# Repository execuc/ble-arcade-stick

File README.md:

BLUETOOTH ARCADE STICK
==========

Project in three part to create a bluetooth arcade stick:
 * [PCB](https://github.com/execuc/ble-arcade-stick/tree/master/pcb)
 * [Bluetooth firmware on NRF51822](https://github.com/execuc/ble-arcade-stick/tree/master/firmware)
 * [Laser cut enclosure with FreeCAD](https://github.com/execuc/ble-arcade-stick/tree/master/cad)

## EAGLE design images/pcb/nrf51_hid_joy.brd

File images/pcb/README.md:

BLUETOOTH ARCADE OR JOYSTICK PCB CONTROLLER
==========

This part contains schematic, layout and gerber files to produce a bluetooth arcade or joystick controller. It is
based on Waveshare NRF51822 module. PCB is made with EAGLE software.

**Caution** : The PCB has not been tested yet.
**Caution** : No reverse polarity

Files
--------------------

 * nrf51_hid_joy.lbr : EAGLE library.
 * nrf51_hid_joy.sch : EAGLE schematic.
 * nrf51_hid_joy.brd : EAGLE board.
 * nrf51_hid_joy.zip : gerber files for PCB.

DIMENSION
--------------------

TODO
--------------------

 * Test PCB.

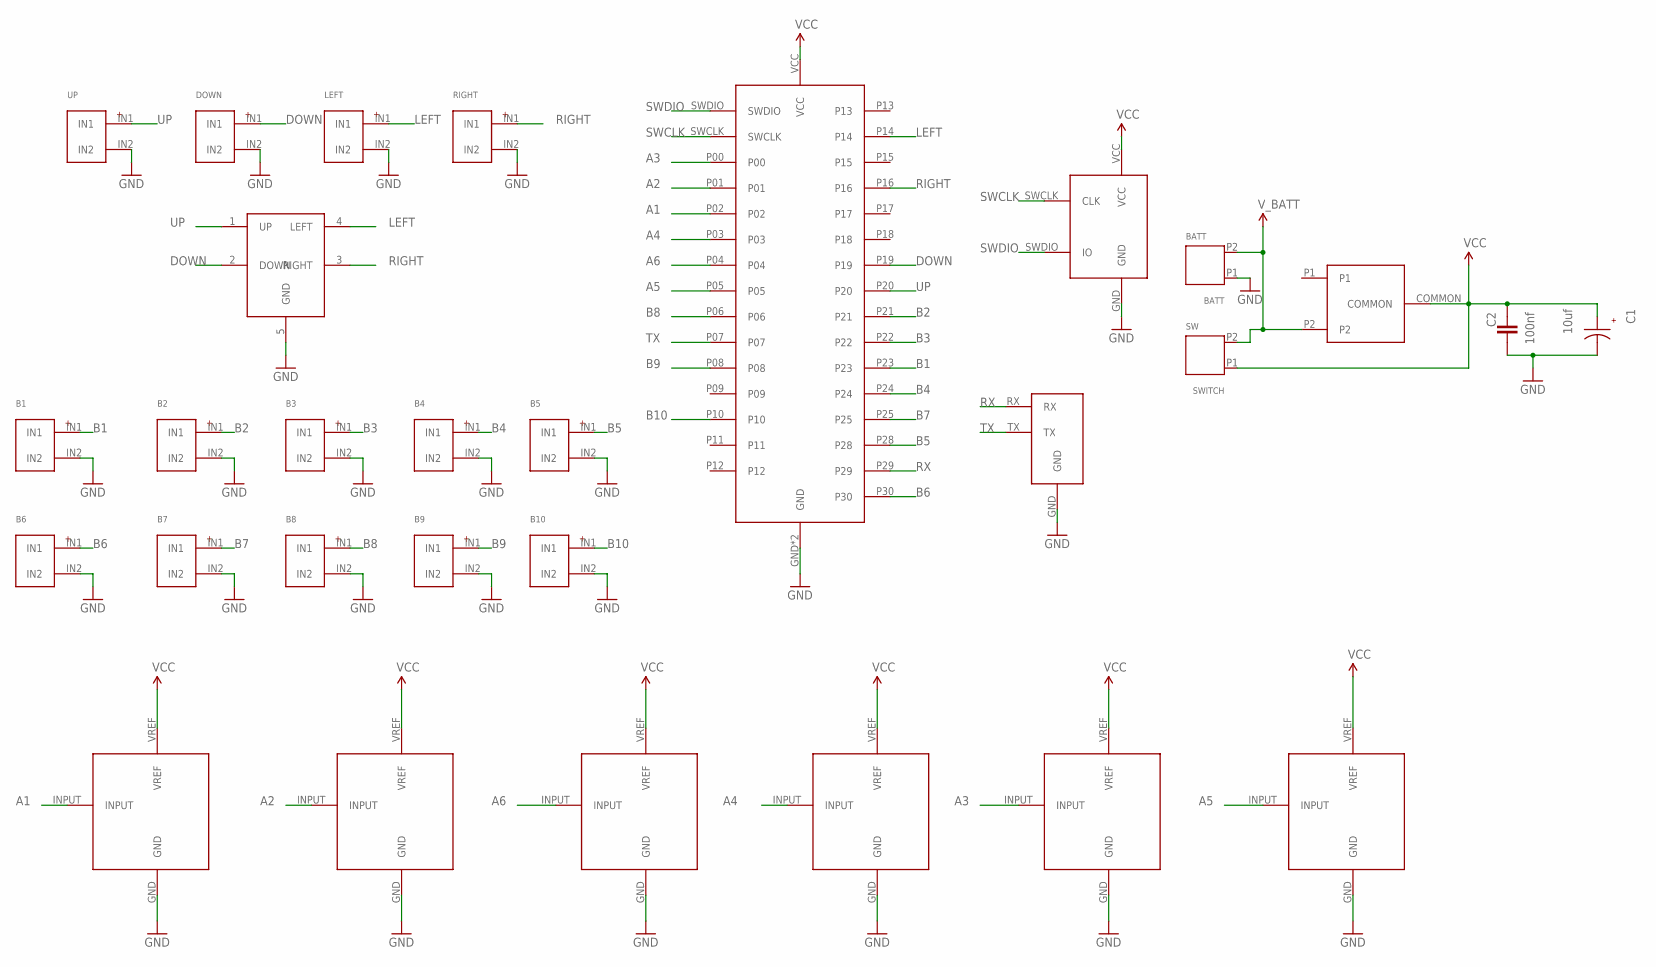
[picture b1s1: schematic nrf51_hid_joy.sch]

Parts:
A1: A1; ANALOG_INPUT
A2: A2; ANALOG_INPUT
A3: A3; ANALOG_INPUT
A4: A4; ANALOG_INPUT
A5: A5; ANALOG_INPUT
A6: A6; ANALOG_INPUT
B1: B1; JST254
B2: B2; JST254
B3: B3; JST254
B4: B4; JST254
B5: B5; JST254
B6: B6; JST254
B7: B7; JST254
B8: B8; JST254
B9: B9; JST254
B10: B10; JST254
BATT: BATT; 2P-3.5
C1: 10uf; CAPA-RAD-MEDIUM
C2: 100nf; 0805
DOWN: DOWN; JST254
LEFT: LEFT; JST254
RIGHT: RIGHT; JST254
SWITCH: SW; 2P-3.5
U$1: NRF51_MODULEBIG; NRF51-MODULE
U$2: NRF51_PROG; PROG_SWD
U$3: NRF51_SERIAL
U$14: 5_5PINS_JOY; 5_PINS_CONNECTOR
U$23: SWITCH; SS-12D00G3
UP: UP; JST254

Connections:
A1: A1.INPUT, U$1.P02
A2: A2.INPUT, U$1.P01
A3: A3.INPUT, U$1.P00
A4: A4.INPUT, U$1.P03
A5: A5.INPUT, U$1.P05
A6: A6.INPUT, U$1.P04
B1: B1.IN1, U$1.P23
B2: B2.IN1, U$1.P21
B3: B3.IN1, U$1.P22
B4: B4.IN1, U$1.P24
B5: B5.IN1, U$1.P28
B6: B6.IN1, U$1.P30
B7: B7.IN1, U$1.P25
B8: B8.IN1, U$1.P06
B9: B9.IN1, U$1.P08
B10: B10.IN1, U$1.P10
DOWN: DOWN.IN1, U$1.P19, U$14.2 (DOWN)
GND: A1.GND, A2.GND, A3.GND, A4.GND, A5.GND, A6.GND, B1.IN2, B2.IN2, B3.IN2, B4.IN2, B5.IN2, B6.IN2, B7.IN2, B8.IN2, B9.IN2, B10.IN2, BATT.P1 (1), C1.2 (-), C2.1, DOWN.IN2, LEFT.IN2, RIGHT.IN2, U$1.GND, U$1.GND2 (GND), U$2.GND, U$3.GND, U$14.5 (GND), UP.IN2
LEFT: LEFT.IN1, U$1.P14, U$14.4 (LEFT)
RIGHT: RIGHT.IN1, U$1.P16, U$14.3 (RIGHT)
RX: U$1.P29, U$3.RX
SWCLK: U$1.SWCLK, U$2.SWCLK (CLK)
SWDIO: U$1.SWDIO, U$2.SWDIO (IO)
TX: U$1.P07, U$3.TX
UP: U$1.P20, U$14.1 (UP), UP.IN1
VCC: A1.VREF, A2.VREF, A3.VREF, A4.VREF, A5.VREF, A6.VREF, C1.1 (+), C2.2, SWITCH.P1 (1), U$1.VCC, U$2.VCC, U$23.COMMON
V_BATT: BATT.P2 (2), SWITCH.P2 (2), U$23.P2

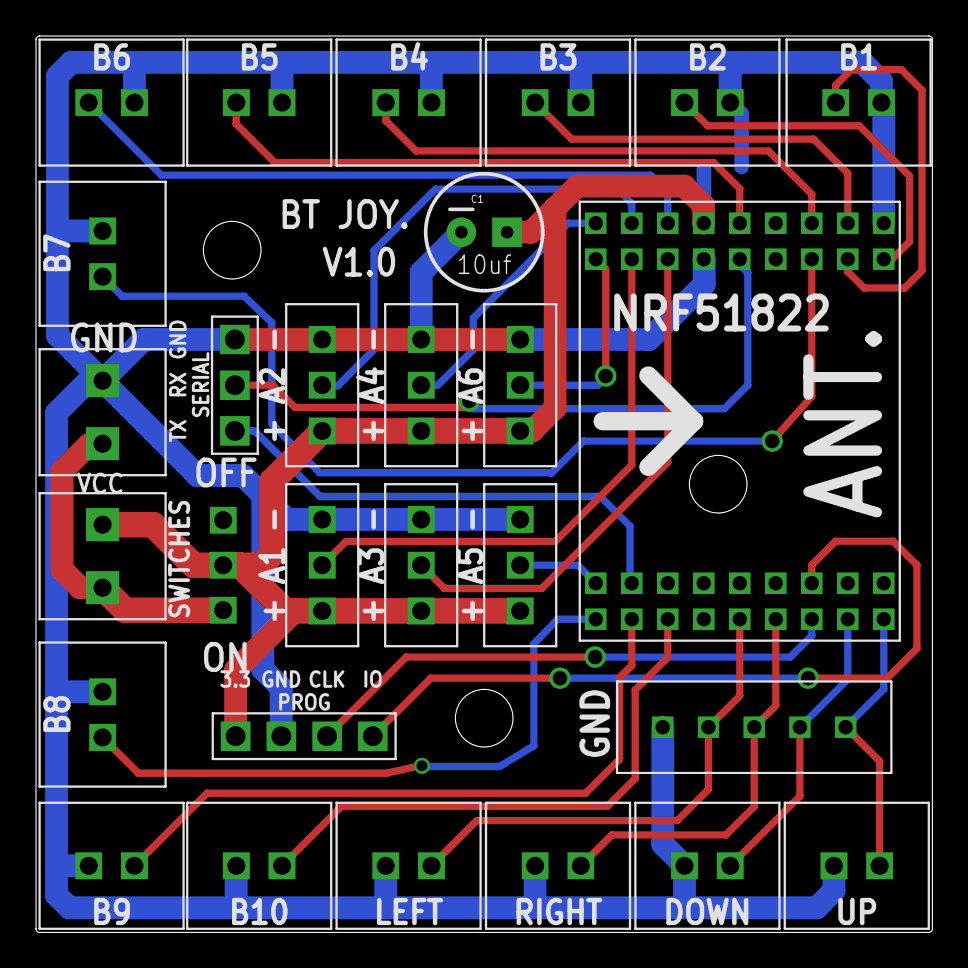
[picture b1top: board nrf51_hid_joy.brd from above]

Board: 4 copper layers, 49.8 x 49.8 mm, 29 parts (1 on the bottom side), 27 nets.

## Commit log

2016-10-12 First commit
    Add PCB part.
2016-10-12 Correct first commit
2016-10-13 Rename repo
2016-10-22 Add firmware file
2016-10-22 Add CAD files
2016-10-22 Correct MD link
2016-10-22 Correct link
2016-10-26 Misc.
    Invert Up/Down Left/Right axis.
2017-01-31 Readme.md
    Add images
